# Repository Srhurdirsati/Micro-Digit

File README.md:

# Micro Digit 

This project is my take on a keyboad; it is orthogonal keyboard with fancy knobs (cause who doesn't like knobs).
The reason I made this project is because I have never loved the keyboard I have had for years now, and I have always wanted to try an orthongonal keyboard. This keyboard is based on the creator keyboard by work louder but I am not paying $350 for a keyboard when I can just build one under $100

## Bill of Materials

Refer To bom.csv

## Images

## How To Set Up

No external wiring is needed, but you can check the schematic in the PCB folder above for more details.

-----------------------------------------------------------------

**Soldering**  

#### *As you have to hand solder all yourself , I would recommend to first solder the PICO on board, then the OLED display and then the keys .*

-----------------------------------------------------

**Firmware**

> Then By pressing boot button on the Pico , insert the able in it with other end on PC end

> Flash The .py firmware file in it .

> This would make the Pico know what it need to do.

---------------------------------------------

**Assembling**

> Now for completing the project , U'll need to assemble the CAD to finalise ther project

>  Start with putting the PCB in Base part .

> After that put the Top plate carefully ( Don't scratch PCB or OLED )

> Lock Everyting in place with M2 screws .

NOW EVERYTHING IS SET UP FINALLY AND THE PROJECT IS COMPLETE . 

` Total = $105 `

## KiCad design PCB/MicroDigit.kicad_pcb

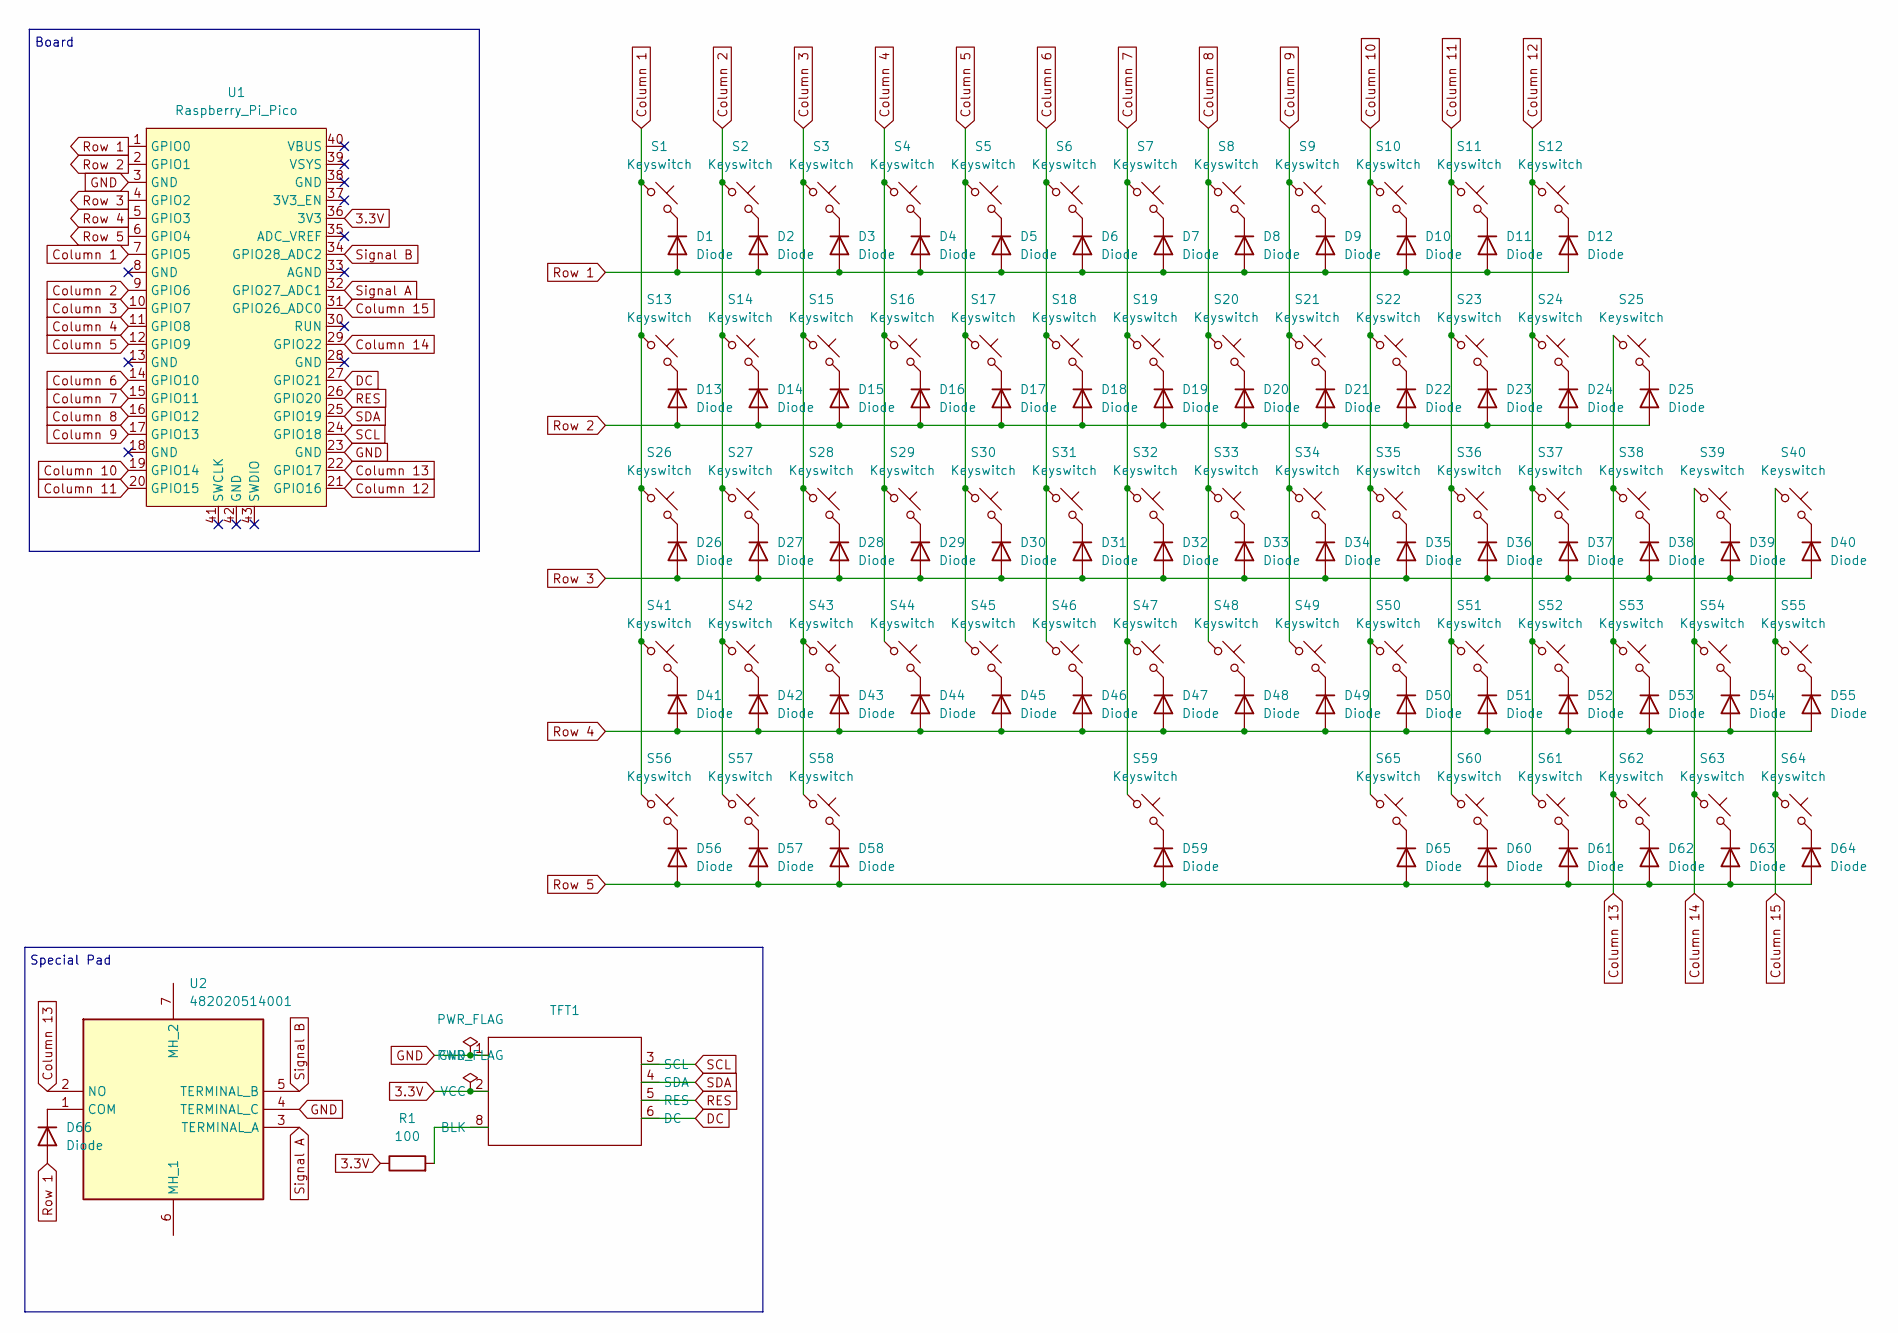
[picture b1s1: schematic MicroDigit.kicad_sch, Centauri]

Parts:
D1, D2, D3, D4, D5, D6, D7, D8, D9, D10, D11, D12, D13, D14, D15, D16, D17, D18, D19, D20, D21, D22, D23, D24, D25, D26, D27, D28, D29, D30, D31, D32, D33, D34, D35, D36, D37, D38, D39, D40, D41, D42, D43, D44, D45, D46, D47, D48, D49, D50, D51, D52, D53, D54, D55, D56, D57, D58, D59, D60, D61, D62, D63, D64, D65, D66: Diode; Diode_SOD-123
R1: 100; Resistor_0402
S1, S2, S3, S4, S5, S6, S7, S8, S9, S10, S11, S13, S14, S15, S16, S17, S18, S19, S20, S21, S22, S23, S24, S25, S26, S27, S28, S29, S30, S31, S32, S33, S34, S35, S36, S37, S38, S39, S42, S43, S44, S45, S46, S47, S48, S49, S50, S51, S52, S53, S54, S55, S60, S61, S62, S63, S64, S65: Keyswitch; Choc_V1_1.00u
S12, S40, S41: Keyswitch; Choc_V1_2.00u
S56, S57, S58: Keyswitch; Choc_V1_1.25u
S59: Keyswitch; Choc_V1_6.25u
TFT1: TFT_1.3_SPI_Module
U1: Raspberry_Pi_Pico; RaspberryPi_Pico_SMD_HandSolder
U2: 482020514001; Mouser Part Number 710-482020514001

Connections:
3.3V: R1.1, TFT1.2 (VCC), U1.36 (3V3)
Column 1: S1.1, S13.1, S26.1, S41.1, S56.1, U1.7 (GPIO5)
Column 2: S2.1, S14.1, S27.1, S42.1, S57.1, U1.9 (GPIO6)
Column 3: S3.1, S15.1, S28.1, S43.1, S58.1, U1.10 (GPIO7)
Column 4: S4.1, S16.1, S29.1, S44.1, U1.11 (GPIO8)
Column 5: S5.1, S17.1, S30.1, S45.1, U1.12 (GPIO9)
Column 6: S6.1, S18.1, S31.1, S46.1, U1.14 (GPIO10)
Column 7: S7.1, S19.1, S32.1, S47.1, S59.1, U1.15 (GPIO11)
Column 8: S8.1, S20.1, S33.1, S48.1, U1.16 (GPIO12)
Column 9: S9.1, S21.1, S34.1, S49.1, U1.17 (GPIO13)
Column 10: S10.1, S22.1, S35.1, S50.1, S65.1, U1.19 (GPIO14)
Column 11: S11.1, S23.1, S36.1, S51.1, S60.1, U1.20 (GPIO15)
Column 12: S12.1, S24.1, S37.1, S52.1, S61.1, U1.21 (GPIO16)
Column 13: S25.1, S38.1, S53.1, S62.1, U1.22 (GPIO17), U2.2 (NO)
Column 14: S39.1, S54.1, S63.1, U1.29 (GPIO22)
Column 15: S40.1, S55.1, S64.1, U1.31 (GPIO26_ADC0)
DC: TFT1.6 (DC), U1.27 (GPIO21)
GND: TFT1.1 (GND), U1.3 (GND), U1.23 (GND), U2.4 (TERMINAL_C)
unnamed: D1.1 (K), S1.2
unnamed: D2.1 (K), S2.2
unnamed: D3.1 (K), S3.2
unnamed: D4.1 (K), S4.2
unnamed: D5.1 (K), S5.2
unnamed: D6.1 (K), S6.2
unnamed: D7.1 (K), S7.2
unnamed: D8.1 (K), S8.2
unnamed: D9.1 (K), S9.2
unnamed: D10.1 (K), S10.2
unnamed: D11.1 (K), S11.2
unnamed: D12.1 (K), S12.2
unnamed: D13.1 (K), S13.2
unnamed: D14.1 (K), S14.2
unnamed: D15.1 (K), S15.2
unnamed: D16.1 (K), S16.2
unnamed: D17.1 (K), S17.2
unnamed: D18.1 (K), S18.2
unnamed: D19.1 (K), S19.2
unnamed: D20.1 (K), S20.2
unnamed: D21.1 (K), S21.2
unnamed: D22.1 (K), S22.2
unnamed: D23.1 (K), S23.2
unnamed: D24.1 (K), S24.2
unnamed: D25.1 (K), S25.2
unnamed: D26.1 (K), S26.2
unnamed: D27.1 (K), S27.2
unnamed: D28.1 (K), S28.2
unnamed: D29.1 (K), S29.2
unnamed: D30.1 (K), S30.2
unnamed: D31.1 (K), S31.2
unnamed: D32.1 (K), S32.2
unnamed: D33.1 (K), S33.2
unnamed: D34.1 (K), S34.2
unnamed: D35.1 (K), S35.2
unnamed: D36.1 (K), S36.2
unnamed: D37.1 (K), S37.2
unnamed: D38.1 (K), S38.2
unnamed: D39.1 (K), S39.2
unnamed: D40.1 (K), S40.2
unnamed: D41.1 (K), S41.2
unnamed: D42.1 (K), S42.2
unnamed: D43.1 (K), S43.2
unnamed: D44.1 (K), S44.2
unnamed: D45.1 (K), S45.2
unnamed: D46.1 (K), S46.2
unnamed: D47.1 (K), S47.2
unnamed: D48.1 (K), S48.2
unnamed: D49.1 (K), S49.2
unnamed: D50.1 (K), S50.2
unnamed: D51.1 (K), S51.2
unnamed: D52.1 (K), S52.2
unnamed: D53.1 (K), S53.2
unnamed: D54.1 (K), S54.2
unnamed: D55.1 (K), S55.2
unnamed: D56.1 (K), S56.2
unnamed: D57.1 (K), S57.2
unnamed: D58.1 (K), S58.2
unnamed: D59.1 (K), S59.2
unnamed: D60.1 (K), S60.2
unnamed: D61.1 (K), S61.2
unnamed: D62.1 (K), S62.2
unnamed: D63.1 (K), S63.2
unnamed: D64.1 (K), S64.2
unnamed: D65.1 (K), S65.2
unnamed: D66.1 (K), U2.1 (COM)
unnamed: R1.2, TFT1.8 (BLK)
RES: TFT1.5 (RES), U1.26 (GPIO20)
Row 1: D1.2 (A), D2.2 (A), D3.2 (A), D4.2 (A), D5.2 (A), D6.2 (A), D7.2 (A), D8.2 (A), D9.2 (A), D10.2 (A), D11.2 (A), D12.2 (A), D66.2 (A), U1.1 (GPIO0)
Row 2: D13.2 (A), D14.2 (A), D15.2 (A), D16.2 (A), D17.2 (A), D18.2 (A), D19.2 (A), D20.2 (A), D21.2 (A), D22.2 (A), D23.2 (A), D24.2 (A), D25.2 (A), U1.2 (GPIO1)
Row 3: D26.2 (A), D27.2 (A), D28.2 (A), D29.2 (A), D30.2 (A), D31.2 (A), D32.2 (A), D33.2 (A), D34.2 (A), D35.2 (A), D36.2 (A), D37.2 (A), D38.2 (A), D39.2 (A), D40.2 (A), U1.4 (GPIO2)
Row 4: D41.2 (A), D42.2 (A), D43.2 (A), D44.2 (A), D45.2 (A), D46.2 (A), D47.2 (A), D48.2 (A), D49.2 (A), D50.2 (A), D51.2 (A), D52.2 (A), D53.2 (A), D54.2 (A), D55.2 (A), U1.5 (GPIO3)
Row 5: D56.2 (A), D57.2 (A), D58.2 (A), D59.2 (A), D60.2 (A), D61.2 (A), D62.2 (A), D63.2 (A), D64.2 (A), D65.2 (A), U1.6 (GPIO4)
SCL: TFT1.3 (SCL), U1.24 (GPIO18)
SDA: TFT1.4 (SDA), U1.25 (GPIO19)
Signal A: U1.32 (GPIO27_ADC1), U2.3 (TERMINAL_A)
Signal B: U1.34 (GPIO28_ADC2), U2.5 (TERMINAL_B)

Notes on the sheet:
Special Pad
Board

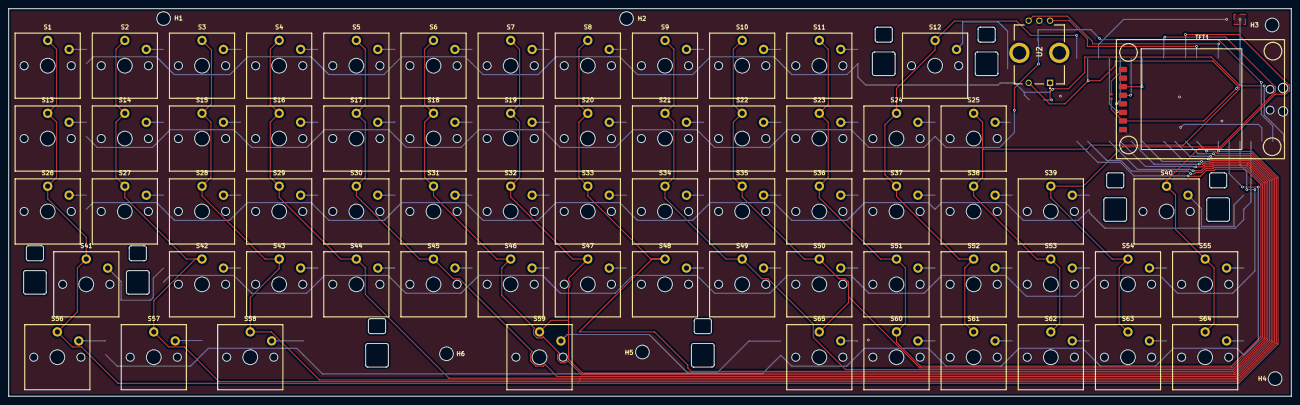
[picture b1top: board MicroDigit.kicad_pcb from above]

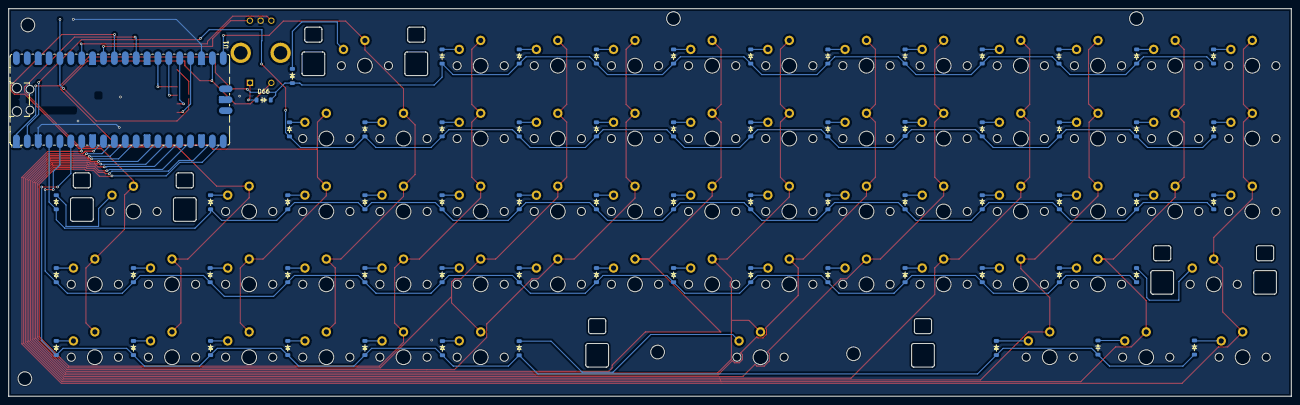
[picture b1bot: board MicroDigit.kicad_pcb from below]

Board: 2 copper layers, 299.2 x 90.4 mm, 141 parts (67 on the bottom side), 95 nets.

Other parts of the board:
H1, H2, H4, H5, H6: MountingHole; MountingHole_3.2mm_M3
H3: MountingHole_3.2mm_M3

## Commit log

2026-03-19 Fix spelling errors and enhance README content
    Corrected spelling errors and improved clarity in project description and usage instructions.
2026-03-19 Revise soldering and firmware instructions in README
    Updated instructions for soldering and firmware flashing.
2026-03-19 Update setup instructions in README.md
    Clarified setup instructions and corrected typos.
2026-03-19 Fix typo in firmware flashing instructions
2026-03-19 Fix typo in README description
2026-03-19 Fix entry for '3D Print With Shipping' in bom.csv
